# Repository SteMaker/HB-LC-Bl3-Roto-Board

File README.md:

# HB-LC-Bl2-24VRain-Board
Selbstbau HomeMatic Hardware mit zwei 24V Rolladenaktoren und einem 230V Rolladenaktor.

## Überblick
**Achtung: Ich übernehme keinerlei Verantwortung für die Sicherheit und Funktionsfähigkeit der Hardware wie auch der Firmware! Die Hardware verwendet Netzspannung 230V ist deshalb lebensgefährlich!**

Firmware: TODO

Ich verwende die Schaltung als Ersatz für eine Rototronic von roto für meine Dachfenster. Der Fensterantrieb und die Verdunklung laufen mit 24V DC Motoren, der Sonnenschutzrollo mit 230V. Der Roto Regensensor kann nicht angeschlossen werden, ich verwende ihn an https://github.com/SteMaker/HB-LC-Bl2-24VRain-Board.

## Dankeschön
Ein dickes, fettes Dankeschön an die homematic community sowas zu ermöglichen, insbesondere an pa-pa, Jérôme und Marco.

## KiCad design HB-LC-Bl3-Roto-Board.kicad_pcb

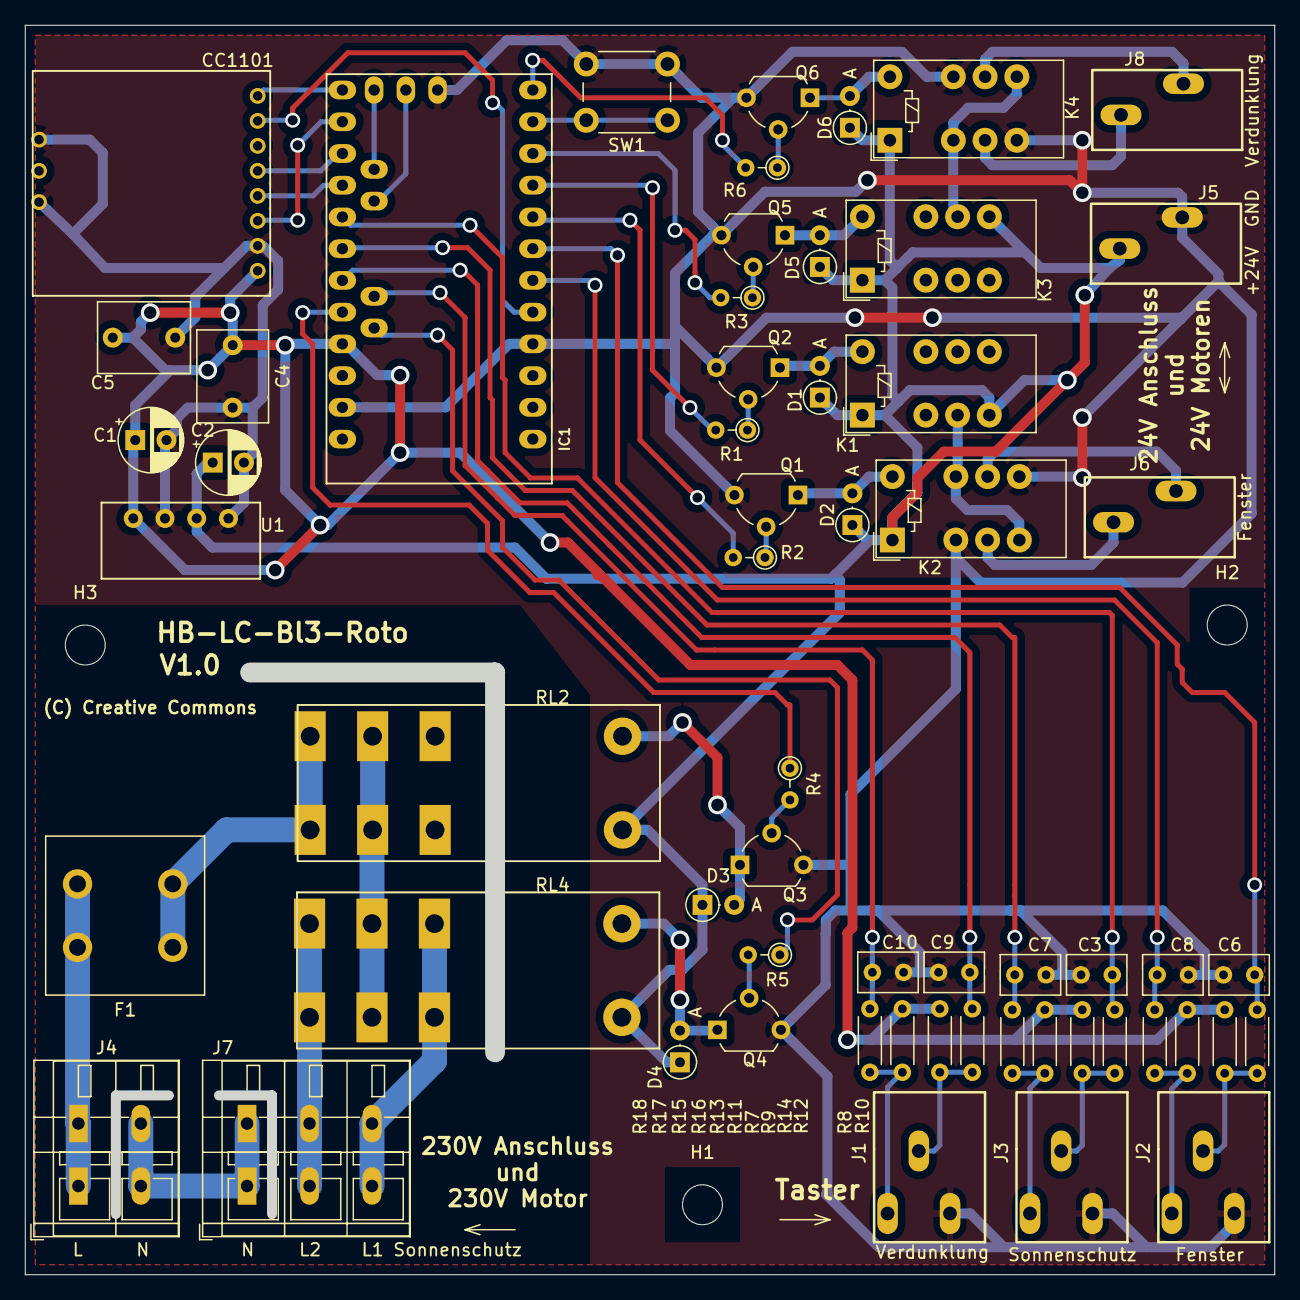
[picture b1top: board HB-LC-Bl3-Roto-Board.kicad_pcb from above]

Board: 2 copper layers, 98.5 x 98.4 mm, 62 parts (0 on the bottom side), 52 nets.

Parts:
C1, C2: 10µF; CP_Radial_D5.0mm_P2.50mm
C3, C6, C7, C8, C9, C10: 100n; C_Rect_L4.6mm_W3.0mm_P2.50mm_MKS02_FKP02
C4, C5: 1u; C_Rect_L7.2mm_W5.5mm_P5.00mm_FKS2_FKP2_MKS2_MKP2
D1, D2, D3, D4, D5, D6: 1N4148; D_DO-35_SOD27_P2.54mm_Vertical_AnodeUp
F1: Fuse; Fuseholder_Cylinder-5x20mm_Schurter_FPG4_Vertical_Closed
H1, H2, H3: MountingHole; MountingHole_3.2mm_M3
IC1: ArduinoProMini; pro_mini
J1: Taster Verdunklung; P-250-403
J2: Taster Fenster; P-250-403
J3: Taster Sonnenschutz; P-250-403
J4: 230V; TerminalBlock_WAGO_236-102_1x02_P5.00mm_45Degree
J5: 24V; P-250-402
J6: Motor Fenster 24V; P-250-402
J7: Motor Sonnenschutz 230V; TerminalBlock_WAGO_236-103_1x03_P5.00mm_45Degree
J8: Motor Verdunklung 24V; P-250-402
K1, K2, K3, K4: G6S-2; Relay_DPDT_Omron_G6S-2
Q1, Q2, Q3, Q4, Q5, Q6: BC337; TO-92L_Wide
R1, R2, R3, R6: 7k5; R_Axial_DIN0204_L3.6mm_D1.6mm_P2.54mm_Vertical
R4, R5: 2k4; R_Axial_DIN0204_L3.6mm_D1.6mm_P2.54mm_Vertical
R7, R8, R11, R12, R15, R17: 10k; R_Axial_DIN0204_L3.6mm_D1.6mm_P5.08mm_Horizontal
R9, R10, R13, R14, R16, R18: 47; R_Axial_DIN0204_L3.6mm_D1.6mm_P5.08mm_Horizontal
RL2, RL4: FINDER-40.61; FIN4061
SW1: SW_Push; SW_PUSH_6mm_H4.3mm
U1: AM1S-xxxxS; SIL-4
U3: CC1101-868MHz-Module; CC1101_Module

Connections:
+3V3: C1.1, C4.1, C5.2, IC1.21, R7.1, R8.1, R11.1, R12.1, R15.1, R17.1, U1.4, U3.1
+24V: C2.1, D1.1, D2.1, D3.1, D4.1, D5.1, D6.1, J5.L2, K1.1, K1.5, K2.1, K3.1, K3.8, K4.1, RL2.A1, RL4.A1, U1.2
/L: F1.2, J4.1
/L_FUSED: F1.1, RL2.14, RL2.24
/M1_A: J6.L1, K2.9
/M1_B: J6.L2, K2.4
/M1_DIR: IC1.8, R2.2
/M1_EN: IC1.9, R1.2
/M2_DIR: IC1.26, R5.1
/M2_EN: IC1.20, R4.1
/M2_L: RL2.11, RL2.21, RL4.11, RL4.21
/M2_L1: J7.3, RL4.12, RL4.22
/M2_L2: J7.2, RL4.14, RL4.24
/M3_A: J8.L2, K4.4
/M3_B: J8.L1, K4.9
/M3_DIR: IC1.12, R6.2
/M3_EN: IC1.10, R3.2
/N: J4.2, J7.1
/RF_CSN: IC1.13, U3.8
/RF_INT: IC1.5, U3.7
/RF_MISO: IC1.15, U3.5
/RF_MOSI: IC1.14, U3.3
/RF_SCLK: IC1.16, U3.4
/TA1: C6.1, IC1.7, R10.1
/TA1_IN: J2.L2, R8.2, R10.2
/TA2: C8.1, IC1.6, R14.1
/TA2_IN: J2.L1, R12.2, R14.2
/TA3: C3.1, IC1.17, R9.1
/TA3_IN: J3.L2, R7.2, R9.2
/TA4: C7.1, IC1.18, R13.1
/TA4_IN: J3.L1, R11.2, R13.2
/TA5: C9.1, IC1.19, R16.1
/TA5_IN: J1.L2, R15.2, R16.2
/TA6: C10.1, IC1.25, R18.1
/TA6_IN: J1.L1, R17.2, R18.2
GND: C1.2, C2.2, C3.2, C4.2, C5.1, C6.2, C7.2, C8.2, C9.2, C10.2, IC1.4, IC1.23, IC1.29, J1.L3, J2.L3, J3.L3, J5.L1, K2.3, K2.8, K4.5, K4.10, Q1.3, Q2.3, Q3.3, Q4.3, Q5.3, Q6.3, SW1.2, U1.1, U1.3, U3.2, U3.10, U3.11
unnamed: D1.2, K1.12, Q2.1
unnamed: D2.2, K2.12, Q1.1
unnamed: D3.2, Q3.1, RL2.A2
unnamed: D4.2, Q4.1, RL4.A2
unnamed: D5.2, K3.12, Q5.1
unnamed: D6.2, K4.12, Q6.1
unnamed: IC1.11, SW1.1
unnamed: K1.4, K2.5, K2.10
unnamed: K3.9, K4.3, K4.8
unnamed: Q1.2, R2.1
unnamed: Q2.2, R1.1
unnamed: Q3.2, R4.2
unnamed: Q4.2, R5.2
unnamed: Q5.2, R3.1
unnamed: Q6.2, R6.1
unnamed: RL2.12, RL2.22

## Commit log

2019-11-09 First version of the schematic
2019-11-09 README updated
2019-11-14 Intermediate commit
2019-11-16 Version 1
2020-02-12 Fixed rotated connector, improved pcb print
    - J6, J5 and J8 are 180° rotated. Still ok to assemble. But some prints
    are no longer readable. Fixed
    - Print of resistor array for R7..R18 is partly wrong. Corrected. Only a
    PCB print issue
2020-04-05 Added missing GND connections for CC1101
2020-04-05 Updated CC101 footprint

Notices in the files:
HB-LC-Bl3-Roto-Board.kicad_pcb:
(C) Creative Commons
